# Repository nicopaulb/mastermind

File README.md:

# Electronic mastermind

Find the followings items : 
- `src` : Embedded code for the board
- `dts` : Project specific Zephyr bindings
- `boards`: Zephyr devicetree overlays for the nRF microcontrollers
- `7seg_driver_module`: Zephyr driver for 7-segments display with 74HC595 shift register
- `flutter-app` : Flutter companion application for interacting with the Mastermind via BLE
- `pcb` : All KiCad files for PCB manufacturing and electric schema

Read more about it here : https://blog.beniserv.fr/posts/mastermind/

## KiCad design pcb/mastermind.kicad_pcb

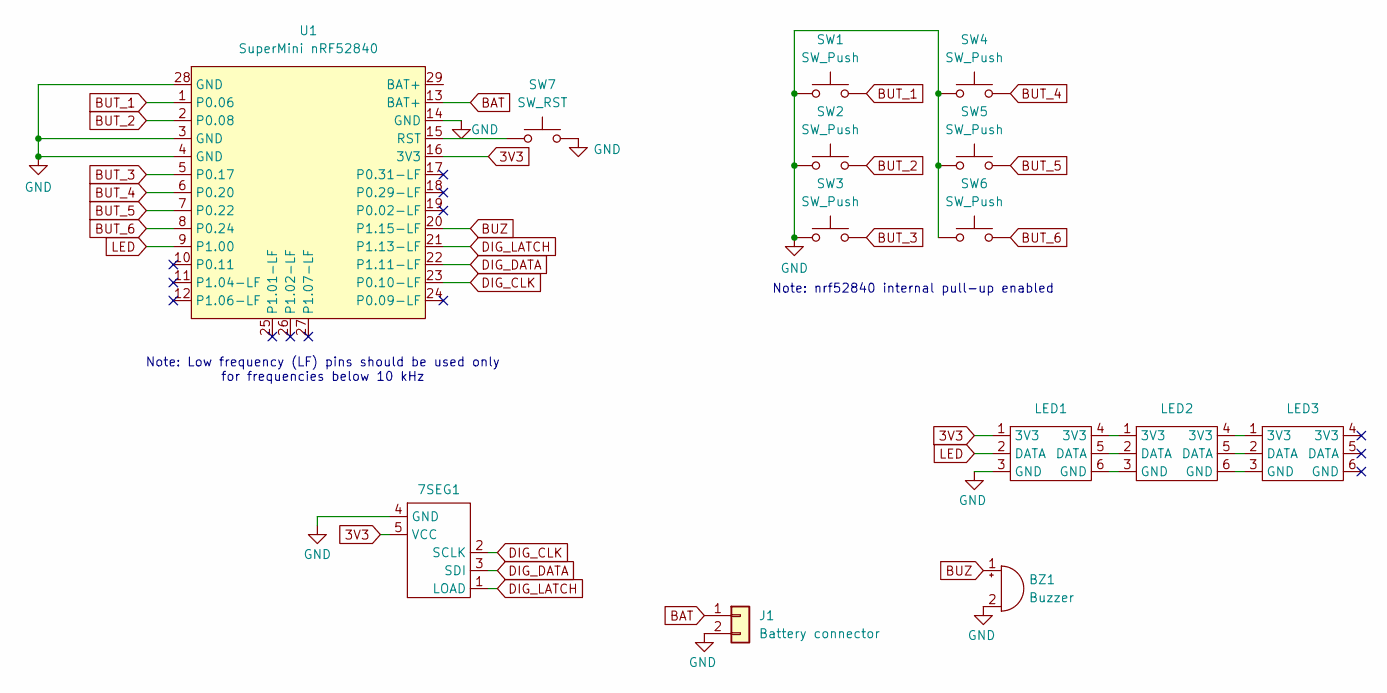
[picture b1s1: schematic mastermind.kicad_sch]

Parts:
7SEG1: 7seg
BZ1: Buzzer; Buzzer_12x9.5RM7.6
J1: Battery connector; JST_PH_B2B-PH-K_1x02_P2.00mm_Vertical
LED1: LED Strip 4 LED
LED2, LED3: LED Strip 2 LED
SW1, SW2, SW3, SW4, SW5, SW6: SW_Push; SW_PUSH-12mm
SW7: SW_RST; SW_PUSH-12mm
U1: SuperMini nRF52840; SuperMini NRF52840

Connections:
3V3: 7SEG1.5 (VCC), LED1.1 (3V3), U1.16 (3V3)
BAT: J1.1, U1.13 (BAT+)
BUT_1: SW1.2, U1.1 (P0.06)
BUT_2: SW2.2, U1.2 (P0.08)
BUT_3: SW3.2, U1.5 (P0.17)
BUT_4: SW4.2, U1.6 (P0.20)
BUT_5: SW5.2, U1.7 (P0.22)
BUT_6: SW6.2, U1.8 (P0.24)
BUZ: BZ1.1 (+), U1.20 (P1.15-LF)
DIG_CLK: 7SEG1.2 (SCLK), U1.23 (P0.10-LF)
DIG_DATA: 7SEG1.3 (SDI), U1.22 (P1.11-LF)
DIG_LATCH: 7SEG1.1 (LOAD), U1.21 (P1.13-LF)
GND: 7SEG1.4 (GND), BZ1.2 (-), J1.2, LED1.3 (GND), SW1.1, SW2.1, SW3.1, SW4.1, SW5.1, SW6.1, SW7.2, U1.3 (GND), U1.4 (GND), U1.14 (GND), U1.28 (GND)
LED: LED1.2 (DATA), U1.9 (P1.00)
unnamed: LED1.4 (3V3), LED2.1 (3V3)
unnamed: LED1.5 (DATA), LED2.2 (DATA)
unnamed: LED1.6 (GND), LED2.3 (GND)
unnamed: LED2.4 (3V3), LED3.1 (3V3)
unnamed: LED2.5 (DATA), LED3.2 (DATA)
unnamed: LED2.6 (GND), LED3.3 (GND)
unnamed: SW7.1, U1.15 (RST)

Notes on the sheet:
Note: nrf52840 internal pull-up enabled
Note: Low frequency (LF) pins should be used only for frequencies below 10 kHz

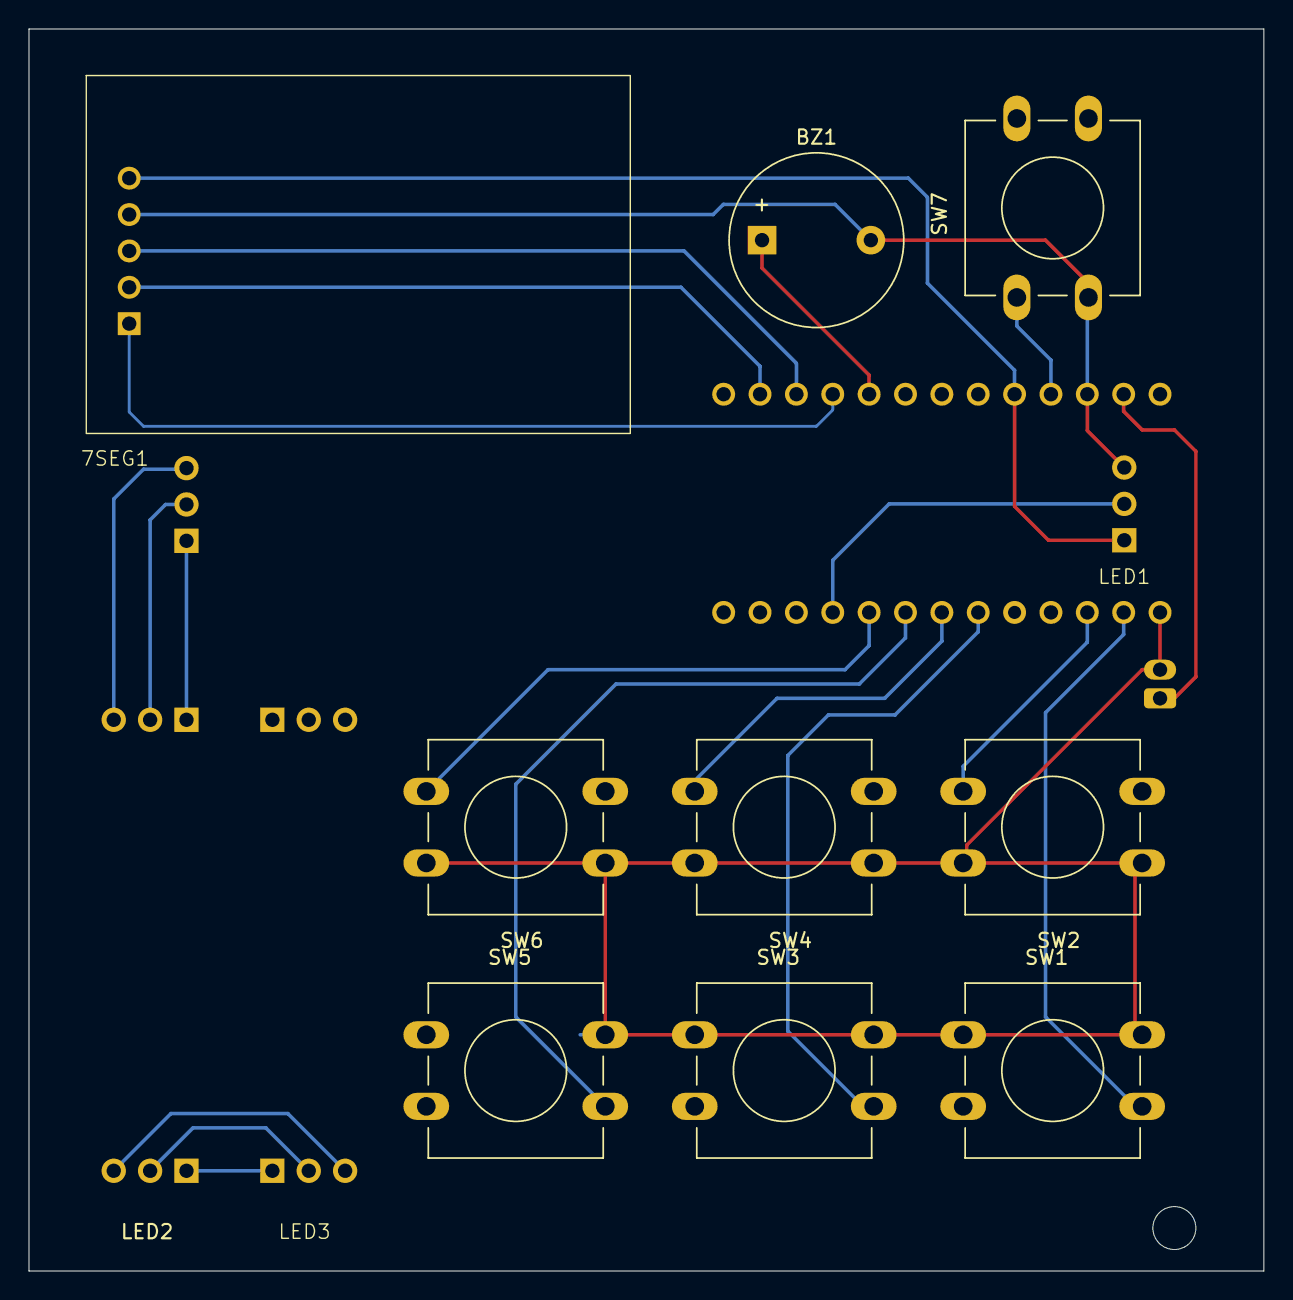
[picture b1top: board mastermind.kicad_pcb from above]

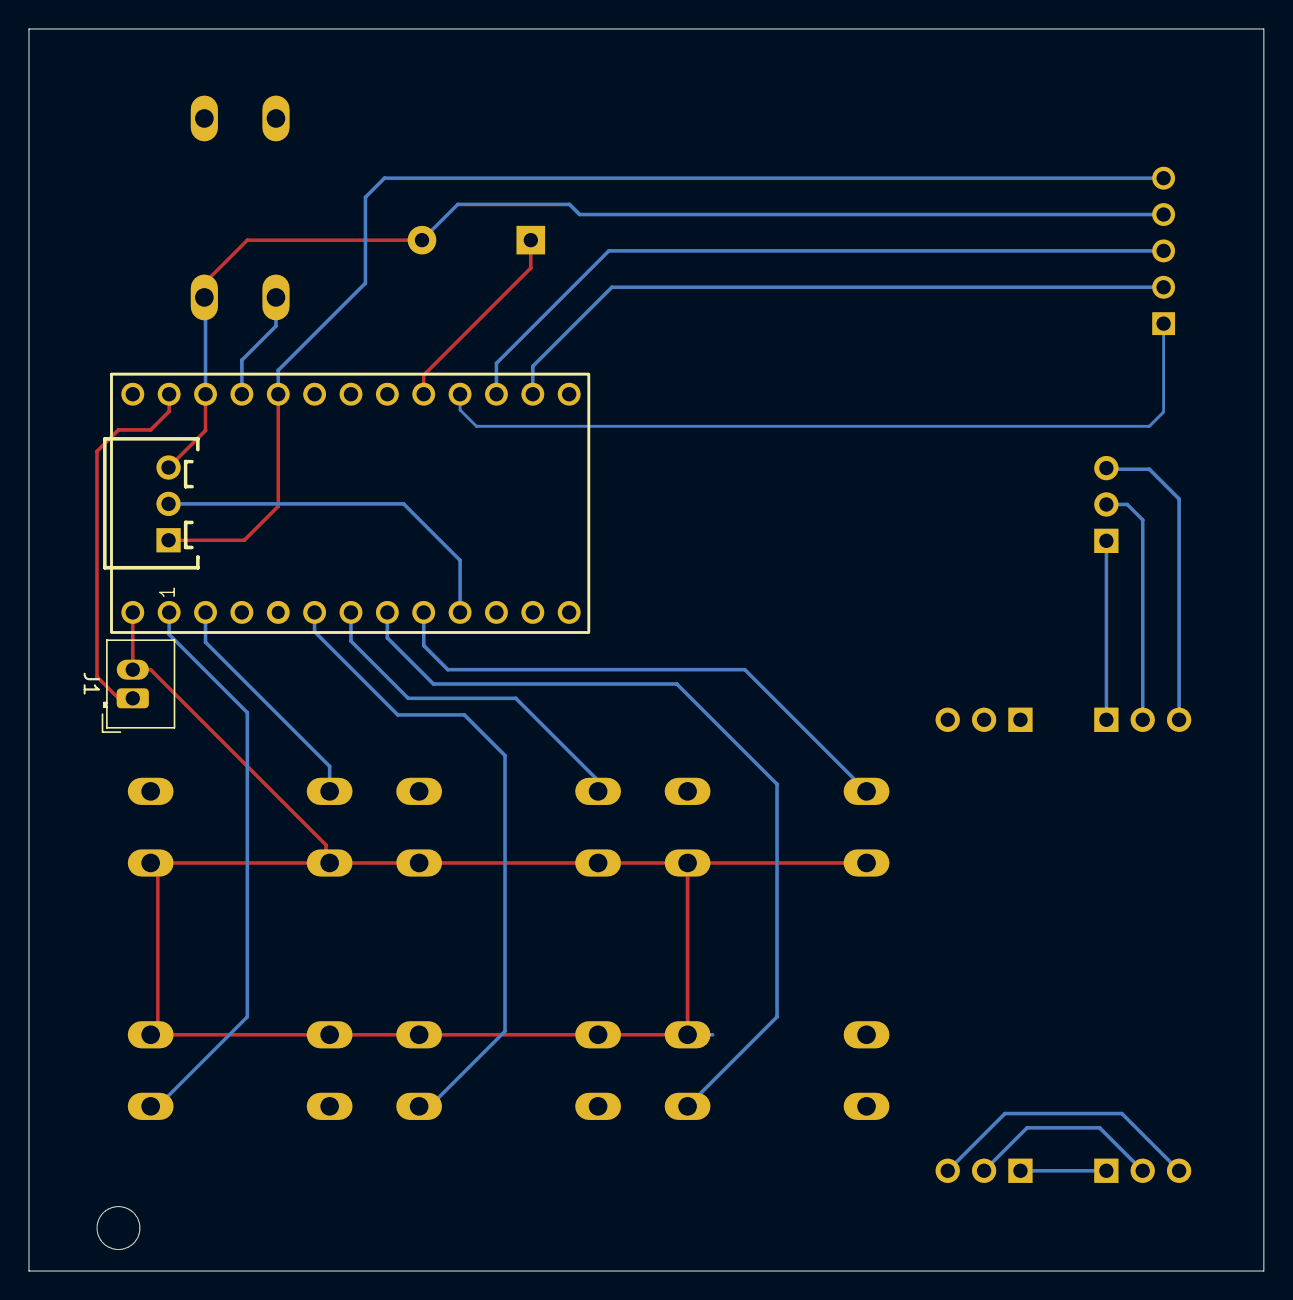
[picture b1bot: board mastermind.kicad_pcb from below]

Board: 2 copper layers, 86.2 x 86.8 mm, 14 parts (2 on the bottom side), 21 nets.

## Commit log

2025-09-30 Initial commit for mastermind
2025-09-30 Adapt sample
2025-10-02 Implement state machine
2025-10-03 fix clues
2025-10-03 fix computes_clues not returning correct value
2025-10-06 keep tentatives history
2025-10-06 remobe nrf52 bindings
2025-10-06 Implement BLE init
2025-10-07 Notify game state via BLE
2025-10-07 Implement BLE command to device
2025-10-07 Remove FSM state object
2025-10-08 Set code manually when BLE command is received
2025-10-08 Update BLE buffer on new round
2025-10-08 Fix all LEDs not being switched off
2025-10-08 fix stack overflow occuring when build optimization is disabled
2025-10-08 Add buzzer (test)
2025-10-09 Improve buzzer
2025-10-09 flutter-app: implement flutter_blue_plus example
2025-10-09 flutter-app: filter mastermind device
2025-10-09 buzzer: add squeleton logic for new sound
2025-10-13 flutter-app: implement device screen
2025-10-13 flutter-app: add popup when round ends
2025-10-13 buzzer: fix concurrent song not being played
2025-10-13 buzzer: add new sound effect
2025-10-13 buzzer: new starting sound
2025-10-13 buttons: debounce input
2025-10-13 flutter-app: add text when tries list is empty
2025-10-20 promicro: create configuration for new board
2025-10-22 buttons: fix buttons on port 1
2025-10-24 seg74hc595: add new custom driver
2025-10-25 seg74hc595: fix digits order
2025-10-25 buzzer: remove buzzer prefix
2025-10-25 dts: update pinout
2025-10-25 display: implement 7 segments display functions
2025-10-25 dts: update pinouts
2025-10-25 seg74hc595: make number of digit configurable via the dts
2025-10-26 seg74hc595: add common-anode property
2025-10-26 buttons: fix color order
2025-10-26 flutter-app: add app icon
2025-10-27 pcb: save kicad files
2025-10-27 pcb: update files
2025-10-28 display: add doc
2025-10-28 doc: create readme files
2025-10-28 doc: update readme
    Added project structure details to the README.
2025-11-04 ble: rename 'reset' characteristic to 'command'
2025-11-06 dts: add 7-seg display node to nrf52dk overlay
2025-11-06 doc: update pcb readme
2025-11-08 leds: fill led array in correct order to match LED strips positions and directions
2025-11-08 pcb: update kicad files
2025-11-16 doc: Add blog link
    Added a link to the blog for more information.
2025-11-16 doc: add youtube video
